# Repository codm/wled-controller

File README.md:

# cod.m WLED Controller (Wi-FI/WLAN)

ESP32 based WLED Controller Wi-Fi to drive adressable LED strips like Neopixel/WS281x/SK6812/WS2801/WS2815/etc using [WLED](https://github.com/Aircoookie/WLED).
Version 0.8 now can be used with 5V *and* 12V strips without the need of external dc-dc converters and we've updated the microcontroller from an ESP8266 to an ESP32. Therefore handling of more LED's and multiple strips are no problem. See https://kno.wled.ge/features/multi-strip/

There now is a button (`IO15`) which can be freely confirugred via WLED. See https://kno.wled.ge/features/macros/#buttons Theoreticly you can also use the flash button on the PCB as an input (`IO0`).

As of WLED 0.13 the first button can be used to do a factory reset by holding it for longer than ten seconds.

* [Wiring Example WS281x/SK6812 5V/12V/24V](https://shop.codm.de/media/e0/8c/7e/1694690940/wiring-scheme-wled-controller-V0.8-WS281x-SK6812.pdf)
* [Wiring Example WS2801/APA102 5V/12V/24V](https://shop.codm.de/media/15/71/33/1694690940/wiring-scheme-wled-controller-V0.8-WS2801.pdf)
* [Wiring Example WS2815 12V](https://shop.codm.de/media/7c/08/47/1694690940/wiring-scheme-wled-controller-V0.8-WS2815.pdf)

More documentation could be foun in the [cod.m Knowledge Base: WLED Controller](https://docs.codm.de/en/wled/controller/).

You can buy it at our webshop: 
* [WLED Controller (Wi-Fi)](https://shop.codm.de/en/automation/wled/30/wled-controller-wlan/wi-fi) (English)
* [WLED Controller (WLAN)](https://shop.codm.de/automation/pixel/30/wlan-pixel-controller-wled) (German)

The board comes preflashed with the current version of WLED, but can be used with any firmware you like, as we've added a flash and reset button for easy flashing.

It can be used with nearly every type of adressable led strips: WS2812B, WS2813, SK6812, APA102, WS2801, LPD8806, TM1814, WS2811, WS2815, GS8208.

Please read the [Adafruit Neopixel Uberguide](https://learn.adafruit.com/adafruit-neopixel-uberguide) on how to work with Neopixels. Antother good starting pint is the [WLED documentation](https://kno.wled.ge/).

Based on the LoxPixel-idea from Dennis (www.unser-smartes-zuhause.de) we've discussed a board layout and in the beginning developed our own software based in Dennis' initial code.
In the end we've settled to expand the absolutely astonishing WLED project with the needed features for Loxone. In Version 0.11 WLED can now understand Loxone values.

## Features

* Espressif ESP32-WROOM-32E 4MB
* usable in 5V, 12V and 24V installations
* up to four lanes of pixel
* drives up to 1000 pixel per lane
* more ESP32 pins are accesible on the back of the PCB
* compact (72x30x16mm)
* reverse polarity protection
* wiring through srew-plug terminal
* real 74AHCT125D level shifter
* detailed instructions
* could be easily (re-)programmed
* open source (CC-BY-NC-SA 4.0)

# Thanks

* [Aircookie](https://github.com/Aircoookie) and the folks from [WLED](https://github.com/Aircoookie/WLED)
* Dennis Henning for the inital idea of the [Lox!Pixel](https://unser-smartes-zuhause.de/2019/10/20/loxpixel-rgbw-neopixel-integration-in-loxone/)
* [m0fa](https://github.com/m0fa)

# License

[CC-BY-NC-SA 4.0](https://creativecommons.org/licenses/by-nc-sa/4.0/de/)

cod.m GmbH, Patrik Mayer, 2022

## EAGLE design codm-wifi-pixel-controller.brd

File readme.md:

# Wi-Fi Pixel Controller

ESP32 based Wi-Fi Pixel Controller to drive adressable LED strips like Neopixel/WS281x/SK6812/WS2801/WS2815/etc using [WLED](https://github.com/Aircoookie/WLED).
Version 0.8 now includes can be used with 5V and 12V strips without the need of external dc-dc converters and we've updated the microcontroller from an ESP8266 to an ESP32. Therefore handling of more LED's and multiple strips are no problem. See https://kno.wled.ge/features/multi-strip/

There now is a button (`IO15`) which can be freely confirugred via WLED. See https://kno.wled.ge/features/macros/#buttons Theoreticly you can also use the flash button on the PCB as an input (`IO0`).

As of WLED 0.13 the first button can be used to do a factory reset by holding it for longer than ten seconds.

* [Wiring Example WS281x/SK6812 5V/12V](https://shop.codm.de/media/pdf/53/e0/3b/Anschlussplan-codm-pixel-controller-V0-8-WS281x-SK6812-1-0.pdf)
* [Wiring Example WS2801/APA102 5V/12V](https://shop.codm.de/media/pdf/81/70/48/Anschlussplan-codm-pixel-controller-V0-8-WS2801-1-0.pdf
* [Wiring Example WS2815 12V](https://shop.codm.de/media/pdf/1b/ac/0b/Anschlussplan-codm-pixel-controller-V0-8-WS2815-1-0.pdf)

You can buy it at our webshop: [Wi-Fi Pixel Controller (WLED)](https://shop.codm.de/automation/pixel/30/wlan-pixel-controller-wled)

The board comes preflashed with the current version of WLED, but can be used with any firmware you like, as we've added a flash and reset button for easy flashing.

It can be used with nearly every type of adressable led strips: WS2812B, WS2813, SK6812, APA102, WS2801, LPD8806, TM1814, WS2811, WS2815, GS8208.

Please read the [Adafruit Neopixel Uberguide](https://learn.adafruit.com/adafruit-neopixel-uberguide) on how to work with Neopixels. Antother good starting pint is the [WLED documentation](https://kno.wled.ge/).

Based on the LoxPixel-idea from Dennis (www.unser-smartes-zuhause.de) we've discussed a board layout and in the beginning developed our own software based in Dennis' initial code.
In the end we've settled to expand the absolutely astonishing WLED project with the needed features for Loxone. In Version 0.11 WLED can now understand Loxone values.

* Espressif ESP32-WROOM-32E 4MB
* usable in 5V and 12V installations
* up to four lanes of pixel
* drives up to 1000 pixel per lane
* more ESP32 pins are accesible on the back of the PCB
* compact (72x30x16mm)
* reverse polarity protection
* wiring through srew-plug terminal
* real 74AHCT125D level shifter
* detailed instructions
* could be easily (re-)programmed
* open source (CC-BY-NC-SA 4.0)

# Thanks
* [Aircookie](https://github.com/Aircoookie) and the folks from [WLED](https://github.com/Aircoookie/WLED)
* Dennis Henning for the inital idea of the [Lox!Pixel](https://unser-smartes-zuhause.de/2019/10/20/loxpixel-rgbw-neopixel-integration-in-loxone/)
* [m0fa](https://github.com/m0fa)

# License
[CC-BY-NC-SA 4.0](https://creativecommons.org/licenses/by-nc-sa/4.0/de/)

cod.m GmbH, Patrik Mayer, 2022

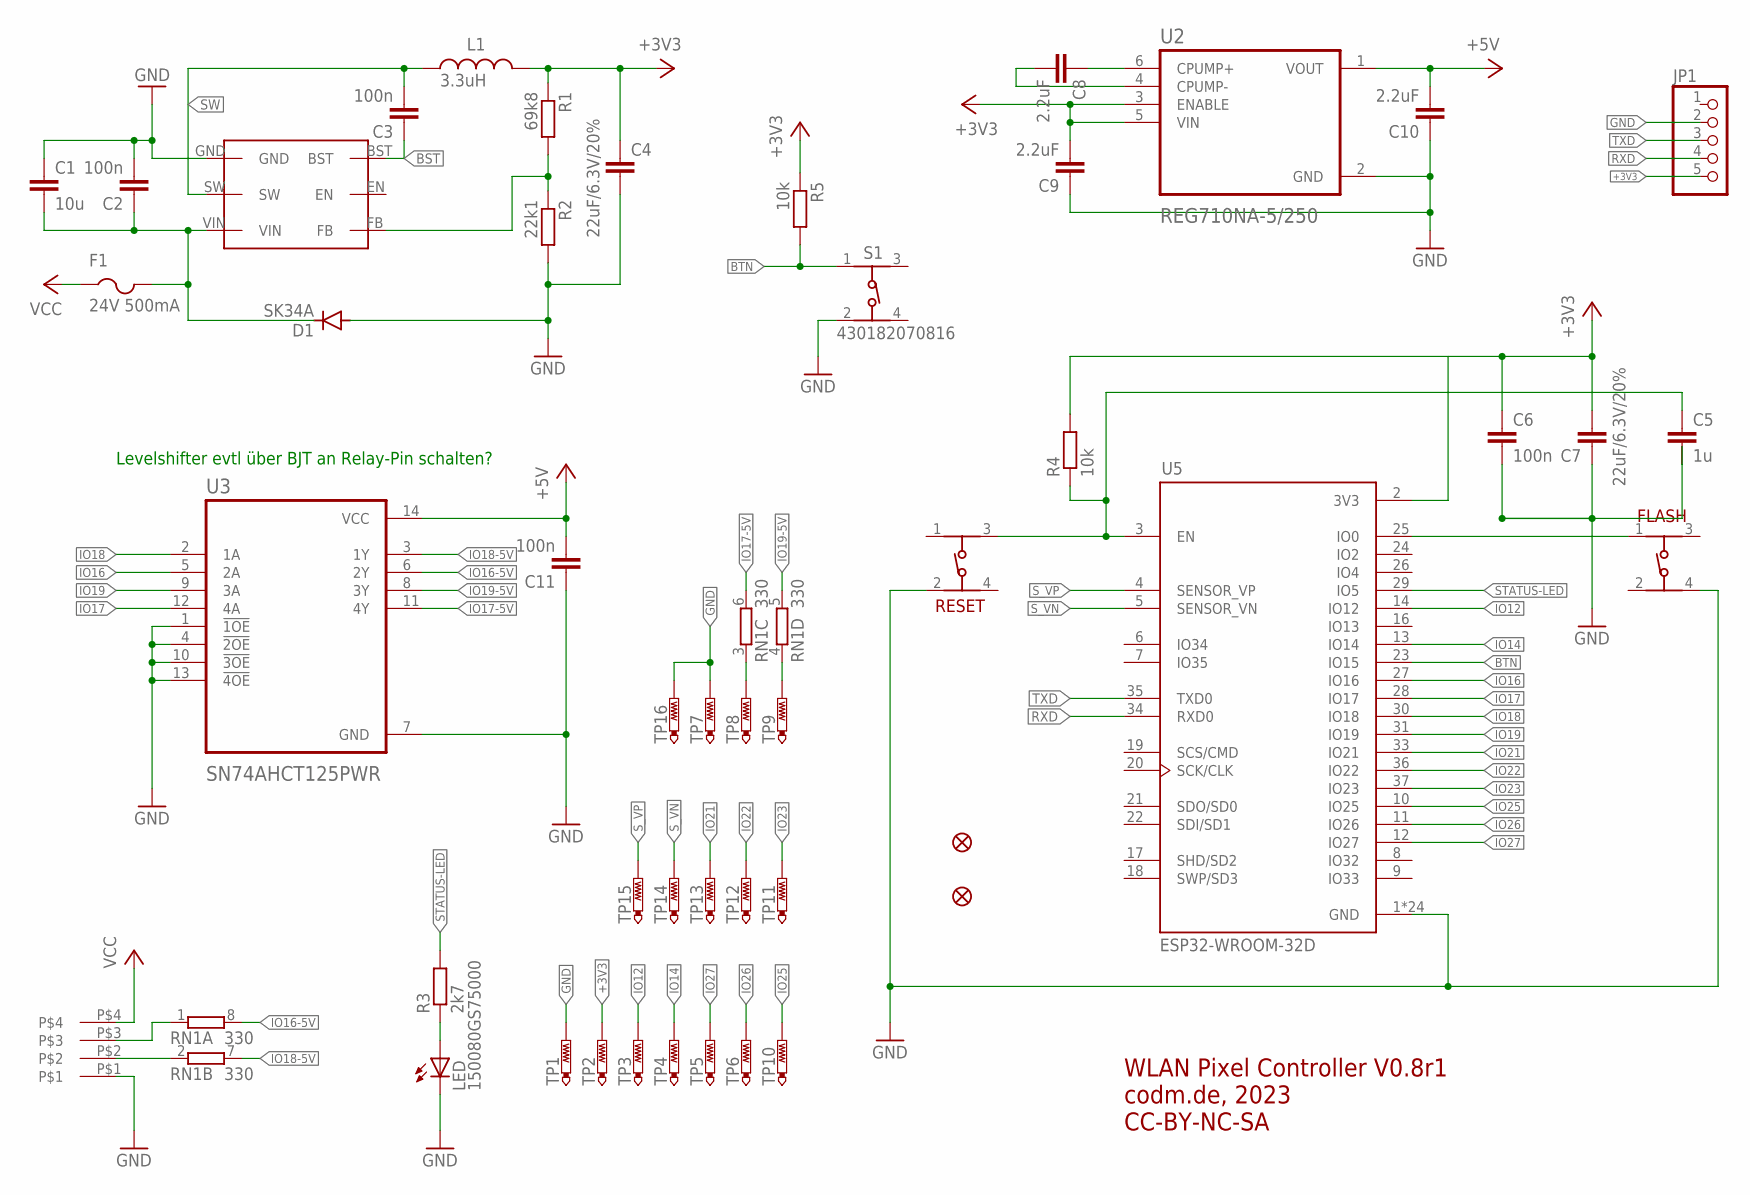
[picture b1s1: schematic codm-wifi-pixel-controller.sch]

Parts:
C1: 10u; C0805K
C2, C3, C6, C11: 100n; C0603K
C4, C7: 22uF/6.3V/20%; C0805K
C5: 1u; C0603K
C8, C9, C10: 2.2uF; C0603K
D1: SK34A; DO214AC
F1: 24V 500mA; R1206
FD1, FD2: FIDUCIAL1X2; FIDUCIAL-1X2
FLASH: 434153017835
JP1: PINHD-1X5; 1X05
L1: 3.3uH; WE-LQ_1812
LED: 150080GS75000; CHIP-LED0805
R1: 69k8; R0603
R2: 22k1; R0603
R3: 2k7; R0603
R4, R5: 10k; R0603
RESET: 434153017835
RN1: 330; EXB38V
S1: 430182070816
TP1, TP2, TP3, TP4, TP5, TP6, TP7, TP8, TP9, TP10, TP11, TP12, TP13, TP14, TP15, TP16: PTR1TP14R; TP14R
U1: AP62XXX-TSOT26
U2: REG710NA-5/250; SOT95P280X145-6N
U3: SN74AHCT125PWR; SOP65P640X120-14N
U5: ESP32-WROOM-32D; MODULE_ESP32-WROOM-32D
U$101: MCV-1,5/4-G-3,81

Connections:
+3V3: C4.1, C6.1, C7.2, C9.2, JP1.5, L1.2, R1.1, R4.2, R5.1, TP2.TP, U2.3 (ENABLE), U2.5 (VIN), U5.2 (3V3)
+5V: C10.2, C11.2, U2.1 (VOUT), U3.14 (VCC)
BST: C3.1, U1.BST
BTN: R5.2, S1.1, U5.23 (IO15)
GND: C1.1, C2.2, C4.2, C5.2, C6.2, C7.1, C9.1, C10.1, C11.1, D1.A, FLASH.4, JP1.2, LED.C, R2.2, RESET.2 (3), S1.2, TP1.TP, TP7.TP, TP16.TP, U1.GND, U2.2 (GND), U3.1 (!1OE), U3.4 (!2OE), U3.7 (GND), U3.10 (!3OE), U3.13 (!4OE), U5.1 (GND), U5.15 (GND), U5.38 (GND), U5.39_1 (GND), U5.39_2 (GND), U5.39_3 (GND), U5.39_4 (GND), U5.39_5 (GND), U5.39_6 (GND), U5.39_7 (GND), U5.39_8 (GND), U5.39_9 (GND), U5.39_10 (GND), U5.39_11 (GND), U5.39_12 (GND), U5.39_13 (GND), U5.39_14 (GND), U5.39_15 (GND), U5.39_16 (GND), U5.39_17 (GND), U5.39_18 (GND), U5.39_19 (GND), U5.39_20 (GND), U5.39_21 (GND), U$101.P$1
GPIO0: FLASH.1, U5.25 (IO0)
IO12: TP3.TP, U5.14 (IO12)
IO14: TP4.TP, U5.13 (IO14)
IO16: U3.5 (2A), U5.27 (IO16)
IO16-5V: RN1.8 (2), U3.6 (2Y)
IO16-5VR: RN1.1, U$101.P$3
IO17: U3.12 (4A), U5.28 (IO17)
IO17-5V: RN1.6 (2), U3.11 (4Y)
IO17-5VR: RN1.3 (1), TP8.TP
IO18: U3.2 (1A), U5.30 (IO18)
IO18-5V: RN1.7 (2), U3.3 (1Y)
IO18-5VR: RN1.2 (1), U$101.P$2
IO19: U3.9 (3A), U5.31 (IO19)
IO19-5V: RN1.5 (2), U3.8 (3Y)
IO19-5VR: RN1.4 (1), TP9.TP
IO21: TP13.TP, U5.33 (IO21)
IO22: TP12.TP, U5.36 (IO22)
IO23: TP11.TP, U5.37 (IO23)
IO25: TP10.TP, U5.10 (IO25)
IO26: TP6.TP, U5.11 (IO26)
IO27: TP5.TP, U5.12 (IO27)
unnamed: C8.1, U2.6 (CPUMP+)
unnamed: R1.2, R2.1, U1.FB
unnamed: LED.A, R3.1
unnamed: C8.2, U2.4 (CPUMP-)
RESET: C5.1, R4.1, RESET.3 (2), U5.3 (EN)
RXD: JP1.4, U5.34 (RXD0)
STATUS-LED: R3.2, U5.29 (IO5)
SW: C3.2, L1.1, U1.SW
S_VN: TP14.TP, U5.5 (SENSOR_VN)
S_VP: TP15.TP, U5.4 (SENSOR_VP)
TXD: JP1.3, U5.35 (TXD0)
VCC: F1.1, U$101.P$4
VCCF: C1.2, C2.1, D1.C, F1.2, U1.VIN

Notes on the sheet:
WLAN Pixel Controller V0.8r1 codm.de, 2023 CC-BY-NC-SA
Levelshifter evtl über BJT an Relay-Pin schalten?

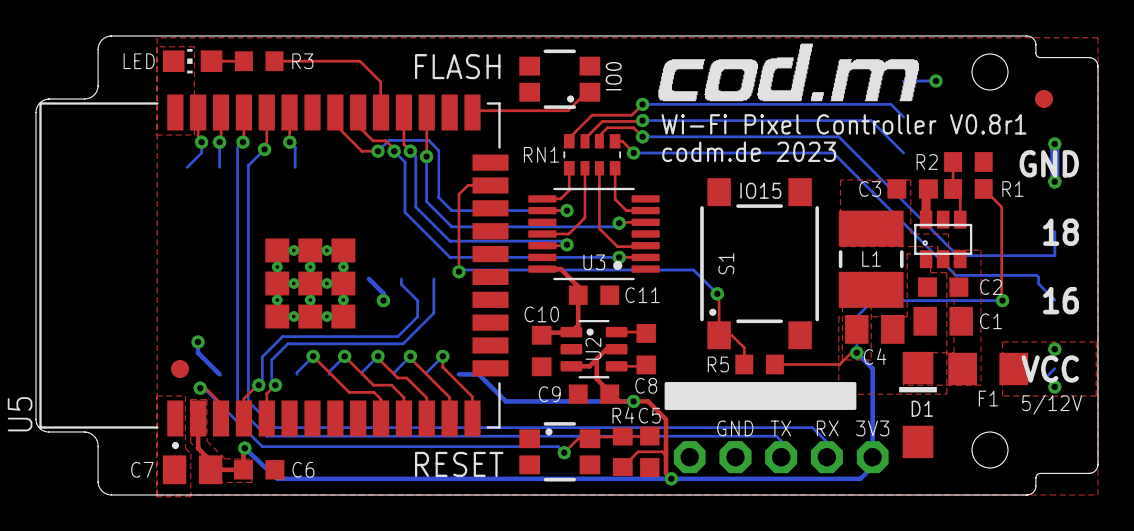
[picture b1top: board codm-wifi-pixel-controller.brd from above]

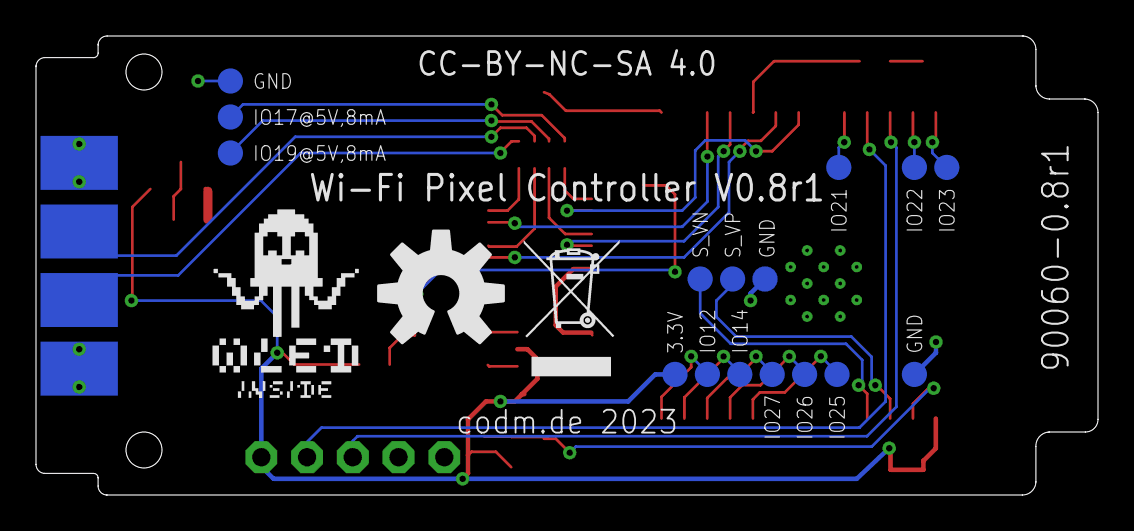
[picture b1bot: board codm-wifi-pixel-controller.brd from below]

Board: 2 copper layers, 59.0 x 25.5 mm, 52 parts (20 on the bottom side), 39 nets.

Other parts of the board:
U$1: CODM-LOGO
U$2: WLED-INSIDE-LOGO-10MM
U$100: WEEE-LOGO-5MM
U$102: OSHW-LOGO-L

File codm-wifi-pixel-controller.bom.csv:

"Qty";"Value";"Device";"Package";"Parts";"Description";"AVAILABILITY";"DATASHEET-URL";"DESCRIPTION";"FRES";"H";"IR";"ISAT";"MF";"MP";"MPN";"OC_FARNELL";"OC_NEWARK";"OPERATION-FORCE";"PACKAGE";"PART-NUMBER";"POPULARITY";"PRICE";"PURCHASE-URL";"Q";"QTY";"RDC-MAX";"SPICEPREFIX";"TP_SIGNAL_NAME";"VALUE";
"2";"";"434153017835";"434153017835";"FLASH, RESET";"WS-TASV J-Bend SMT Tact Switch 3.5x2.9 mm";"";"https://www.we-online.com/catalog/datasheet/434153017835.pdf";"";"";"1.7mm";"";"";"";"";"";"";"";"350g";"";"434153017835";"";"";"";"";" 4000 ";"";"";"";"";
"1";"";"PINHD-1X5";"1X05";"JP1";"PIN HEADER";"";"";"";"";"";"";"";"";"";"";"";"";"";"";"";"69";"";"";"";"";"";"";"";"";
"4";"100n";"C-EUC0603K";"C0603K";"C2, C3, C6, C11";"CAPACITOR, European symbol";"";"";"";"";"";"";"";"";"";"";"";"";"";"";"";"30";"";"";"";"";"";"C";"";"";
"2";"10k";"R-EU_R0603";"R0603";"R4, R5";"RESISTOR, European symbol";"";"";"";"";"";"";"";"";"";"";"";"";"";"";"";"70";"";"";"";"";"";"R";"";"";
"1";"10u";"C-EUC0805K";"C0805K";"C1";"CAPACITOR, European symbol";"";"";"";"";"";"";"";"";"";"";"";"";"";"";"";"52";"";"";"";"";"";"C";"";"";
"1";"150080RS75000";"LEDCHIP-LED0805";"CHIP-LED0805";"LED";"LED";"";"";"";"";"";"";"";"";"";"";"";"";"";"";"";"";"";"";"";"";"";"";"";"";
"1";"1u";"C-EUC0603K";"C0603K";"C5";"CAPACITOR, European symbol";"";"";"";"";"";"";"";"";"";"";"";"";"";"";"";"30";"";"";"";"";"";"C";"";"";
"3";"2.2uF";"C-EUC0603K";"C0603K";"C8, C9, C10";"CAPACITOR, European symbol";"";"";"";"";"";"";"";"";"";"";"";"";"";"";"";"30";"";"";"";"";"";"C";"";"";
"1";"22k1";"R-EU_R0603";"R0603";"R2";"RESISTOR, European symbol";"";"";"";"";"";"";"";"";"";"";"";"";"";"";"";"70";"";"";"";"";"";"R";"";"";
"2";"22uF/6.3V/20%";"C-EUC0805K";"C0805K";"C4, C7";"CAPACITOR, European symbol";"";"";"";"";"";"";"";"";"";"";"";"";"";"";"";"52";"";"";"";"";"";"C";"";"";
"1";"24V 500mA";"PTCFUSE-1206";"R1206";"F1";"PTC fuses, resettable thermistors";"";"";"";"";"";"";"";"";"";"";"";"";"";"";"";"";"";"";"";"";"";"";"";"";
"1";"2k7";"R-EU_R0603";"R0603";"R3";"RESISTOR, European symbol";"";"";"";"";"";"";"";"";"";"";"";"";"";"";"";"70";"";"";"";"";"";"R";"";"";
"1";"3.3uH";"WE-LQ_1812_744045003";"WE-LQ_1812";"L1";"WE-LQ SMD Inductor";"";"https://katalog.we-online.com/pbs/datasheet/744045003.pdf";"";"58MHz";"";"1.4A";"2.7A";"";"";"";"";"";"";"";" 744045003 ";"";"";"";" 45 ";"";"0.13Ohm";"";"";"3.3uH";
"1";"330";"4R-NEXB38V";"EXB38V";"RN1";"Array Chip Resistor";"";"";"";"";"";"";"";"";"";"";"unknown";"unknown";"";"";"";"5";"";"";"";"";"";"";"";"";
"1";"430182070816";"430182070816";"430182070816";"S1";"WS-TASV SMT Tact Switch 6x6 mm";"";"https://www.we-online.com/catalog/datasheet/430182070816.pdf";"";"";"7mm";"";"";"";"";"";"";"";"160g";"";"430182070816";"";"";"";"";"550";"";"";"";"430182070816";
"1";"69k8";"R-EU_R0603";"R0603";"R1";"RESISTOR, European symbol";"";"";"";"";"";"";"";"";"";"";"";"";"";"";"";"70";"";"";"";"";"";"R";"";"";
"1";"AP62XXX-TSOT26";"AP62XXX-TSOT26";"AP62XXX-TSOT26";"U1";"";"";"";"";"";"";"";"";"";"";"";"";"";"";"";"";"";"";"";"";"";"";"";"";"";
"1";"ESP-WROOM-32";"ESP-WROOM-32";"ESP-WROOM-32";"U4";"";"";"";"";"";"";"";"";"";"";"";"";"";"";"";"";"";"";"";"";"";"";"";"";"";
"1";"MCV-1,5/4-G-3,81";"MCV-1,5/4-G-3,81";"MCV-1,5/4-G-3,81";"U$101";"";"";"";"";"";"";"";"";"";"";"";"";"";"";"";"";"";"";"";"";"";"";"";"";"";
"16";"PTR1TP14R";"PTR1TP14R";"TP14R";"TP1, TP2, TP3, TP4, TP5, TP6, TP7, TP8, TP9, TP10, TP11, TP12, TP13, TP14, TP15, TP16";"TEST PIN";"";"";"";"";"";"";"";"";"";"";"";"";"";"";"";"1";"";"";"";"";"";"";"";"";
"1";"REG710NA-5/250";"REG710NA-5/250";"SOT95P280X145-6N";"U2";"Check prices";"In Stock";"";" 30-mA Switched-Cap DC-DC Converter with fixed 5-V Output 6-SOT-23 -40 to 85 ";"";"";"";"";"Texas Instruments";"REG710NA-5/250";"";"";"";"";"SOT-23-6 Texas Instruments";"";"";"None";"https://pricing.snapeda.com/search/part/REG710NA-5/250/?ref=eda";"";"";"";"";"";"";
"1";"SK34A";"DIODE-DO214AC";"DO214AC";"D1";"DIODE";"";"";"";"";"";"";"";"";"";"";"";"";"";"";"";"14";"";"";"";"";"";"";"";"";
"1";"SN74AHCT125PWR";"SN74AHCT125PWR";"SOP65P640X120-14N";"U3";"Check availability";"In Stock";"";" Quadruple Bus Buffer Gates With 3-State Outputs 14-TSSOP -40 to 125 ";"";"";"";"";"Texas Instruments";"SN74AHCT125PWR";"";"";"";"";"TSSOP-14 Texas Instruments";"";"";"None";"https://pricing.snapeda.com/search/part/SN74AHCT125PWR/?ref=eda";"";"";"";"";"";"";

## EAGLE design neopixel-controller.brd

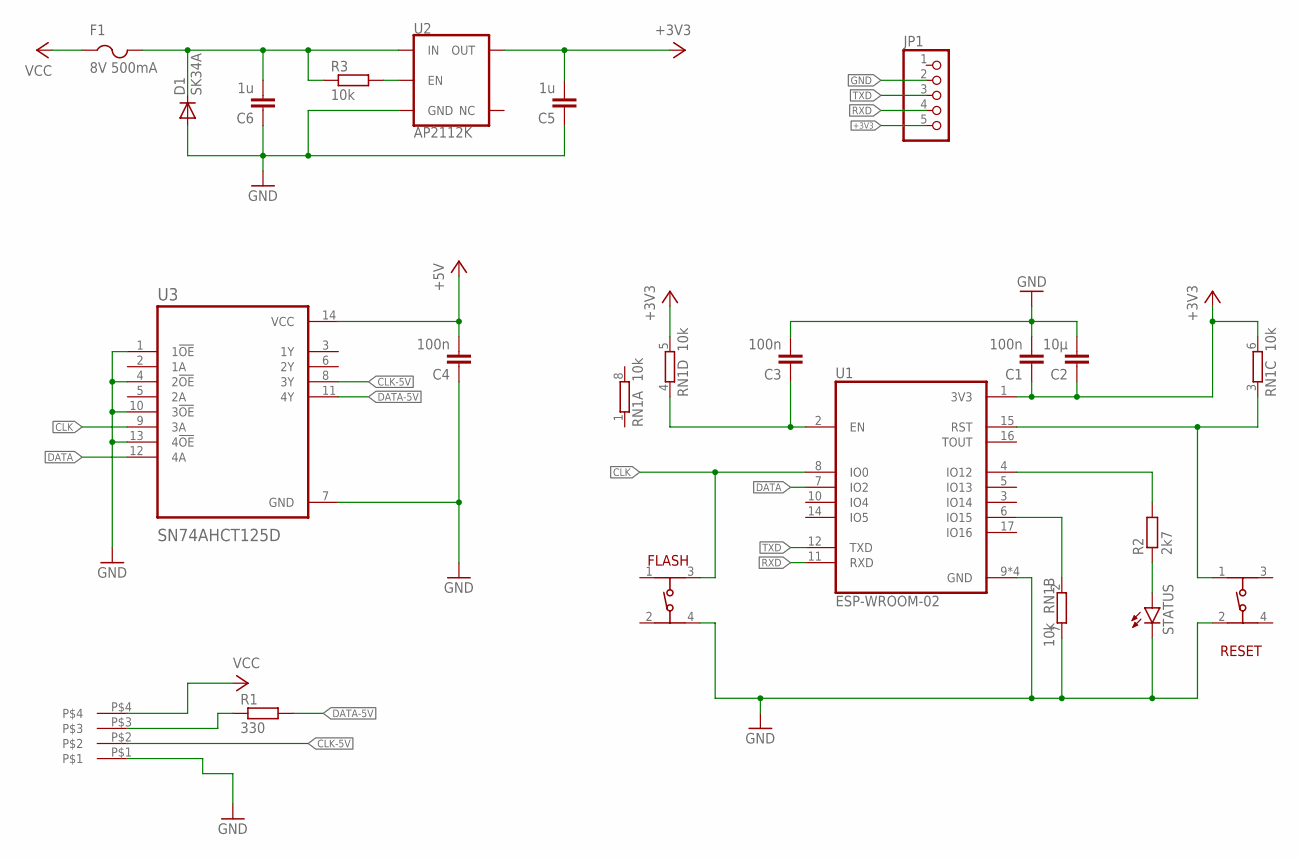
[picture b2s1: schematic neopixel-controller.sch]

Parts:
C1, C3, C4: 100n; C0805
C2: 10µ; C0805
C5, C6: 1u; C0805
D1: SK34A; DO214AC
F1: 8V 500mA; R1206
FLASH: 434153017835
JP1: PINHD-1X5; 1X05
R1: 330; R0805
R2: 2k7; R0805
R3: 10k; R0805
RESET: 434153017835
RN1: 10k; EXB38V
STATUS: LEDCHIPLED_0805; CHIPLED_0805
U1: ESP-WROOM-02; MODULE_ESP-WROOM-02
U2: AP2112K; SOT23-5
U3: SN74AHCT125D; SOIC127P600X175-14N
U$101: MCV-1,5/4-G-3,81

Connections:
+3V3: C1.1, C2.1, C5.2, JP1.5, RN1.5 (2), RN1.6 (2), U1.1 (3V3), U2.5 (OUT)
+5V: C4.2, C6.2, D1.C, F1.2, R3.1, U2.1 (IN), U3.14 (VCC)
BOOTMODE: RN1.2 (1), U1.6 (IO15)
CHIPEN: C3.1, RN1.4 (1), U1.2 (EN)
CLK: FLASH.3 (2), U1.8 (IO0), U3.9 (3A)
CLK-5V: U3.8 (3Y), U$101.P$2
DATA: U1.7 (IO2), U3.12 (4A)
DATA-5V: R1.2, U3.11 (4Y)
DATA-5VR: R1.1, U$101.P$3
GND: C1.2, C2.2, C3.2, C4.1, C5.1, C6.1, D1.A, FLASH.4, JP1.2, RESET.2 (3), RN1.7 (2), STATUS.C, U1.9 (GND), U1.13 (GND), U1.18 (GND), U1.19 (GND), U2.2 (GND), U3.1 (1!OE), U3.4 (2!OE), U3.7 (GND), U3.10 (3!OE), U3.13 (4!OE), U$101.P$1
unnamed: R3.2, U2.3 (EN)
unnamed: R2.1, STATUS.A
RST: RESET.1, RN1.3 (1), U1.15 (RST)
RXD: JP1.4, U1.11 (RXD)
STATLED: R2.2, U1.4 (IO12)
TXD: JP1.3, U1.12 (TXD)
VCC: F1.1, U$101.P$4

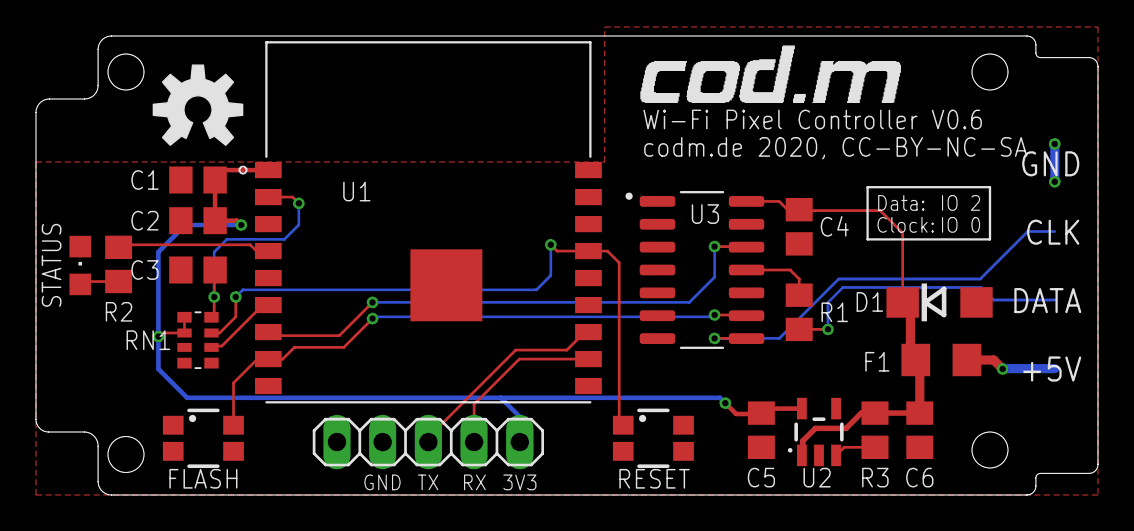
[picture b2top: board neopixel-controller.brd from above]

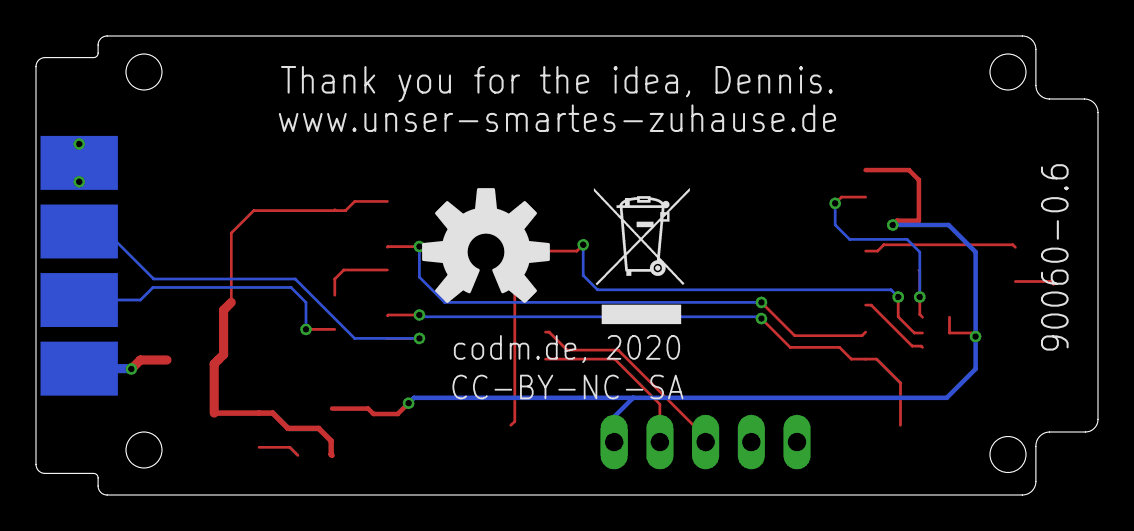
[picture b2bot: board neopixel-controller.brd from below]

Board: 2 copper layers, 59.0 x 25.5 mm, 24 parts (3 on the bottom side), 17 nets.

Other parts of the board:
U$1: CODM-LOGO
U$2: OSHW-LOGO-M
U$100: WEEE-LOGO-5MM
U$102: OSHW-LOGO-L

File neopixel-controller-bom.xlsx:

| neopixel controller 0.6
 | Qty | Spalte1 | Value | Device | Package | Parts | Description
 | 2 | 40 |  | 434153017835 | 434153017835 | FLASH, RESET | WS-TASV J-Bend SMT Tact Switch 3.5x2.9 mm
 | 1 | 20 |  | LEDCHIPLED_0805 | CHIPLED_0805 | STATUS | LED
 | 1 | 20 |  | PINHD-1X5 | 1X05 | JP1 | PIN HEADER
 | 3 | 60 | 100n | C-EUC0805 | C0805 | C1, C3, C4 | CAPACITOR, European symbol
 | 1 | 20 | 10k | 4R-NEXB38V | EXB38V | RN1 | Array Chip Resistor
 | 1 | 20 | 10k | R-EU_R0805 | R0805 | R3 | RESISTOR, European symbol
 | 1 | 20 | 10µ | C-EUC0805 | C0805 | C2 | CAPACITOR, European symbol
 | 2 | 40 | 1u | C-EUC0805 | C0805 | C5, C6 | CAPACITOR, European symbol
 | 1 | 20 | 2k7 | R-EU_R0805 | R0805 | R2 | RESISTOR, European symbol
 | 1 | 20 | 330 | R-EU_R0805 | R0805 | R1 | RESISTOR, European symbol
 | 1 | 20 | 8V 500mA | PTCFUSE-1206 | R1206 | F1 | PTC fuses, resettable thermistors
 | 1 | 20 | AP2112K | V_REG_AP2112K-3.3V | SOT23-5 | U2 | AP2112 - 600mA CMOS LDO Regulator w/ Enable
 | 1 | 20 | ESP-WROOM-02 | ESP-WROOM-02 | MODULE_ESP-WROOM-02 | U1 | Wi-Fi Module w/ESP8266 802.11b/g/n 20dBm 20x18x3mm
 | 1 | 20 | MCV-1,5/4-G-3,81 | MCV-1,5/4-G-3,81 | MCV-1,5/4-G-3,81 | U$101
 | 1 | 20 | SK34A | DIODE-DO214AC | DO214AC | D1 | DIODE
 | 1 | 20 | SN74AHCT125D | SN74AHCT125D | SOIC127P600X175-14N | U3 | Check prices
 |  |  |  | 20

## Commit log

2020-08-11 v 0.4, initial git
2020-09-03 changed 3d model
2020-09-10 added 74ahct125, rework for v0.5
2020-09-17 v0.5 pr
2020-10-05 V0.5
2020-10-26 fixed OE of 74AHCT125
2020-11-23 minor changes in schematic
2020-11-23 added readme, initial github release
2021-04-12 v0.6 with placeholder for pick&place
2021-10-04 development version 0.7
2021-10-06 version with TLV767 and bigger thermal via/planes
2021-10-29 prototype 0.7.2
2022-01-24 V0.7.3 - forgot reverse polarity protection
2022-01-24 added reverse polarity protection
2022-02-02 new version 0.7.4 with fixes
2022-02-04 finetuning 0.7.4
2022-02-23 after prototype 0.7.4 - final 0.8
2022-03-29 final V0.8, edited readme
2022-03-29 refined readme
2023-02-08 clenaup
2023-02-22 better esp32 footprint, minor rearangements
2023-02-22 updated year on top
2023-02-23 better fiducials
2023-02-23 fixed groundplane
2023-10-18 updated wiring sheme links

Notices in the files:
neopixel-controller.brd:
codm.de 2020, CC-BY-NC-SA
parts and their libraries:
SparkFun-Aesthetics: Licensing: Creative Commons ShareAlike 4.0 International - https://creativecommons.org/licenses/by-sa/4.0
434153017835_Eagle_WS-TASV_rev20a: Copyright: Würth Elektronik
